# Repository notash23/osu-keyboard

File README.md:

# osu-keyboard

This is a keyboard with two assignable buttons. It has been built using RP2040. It also has two customizable RGB backlights.

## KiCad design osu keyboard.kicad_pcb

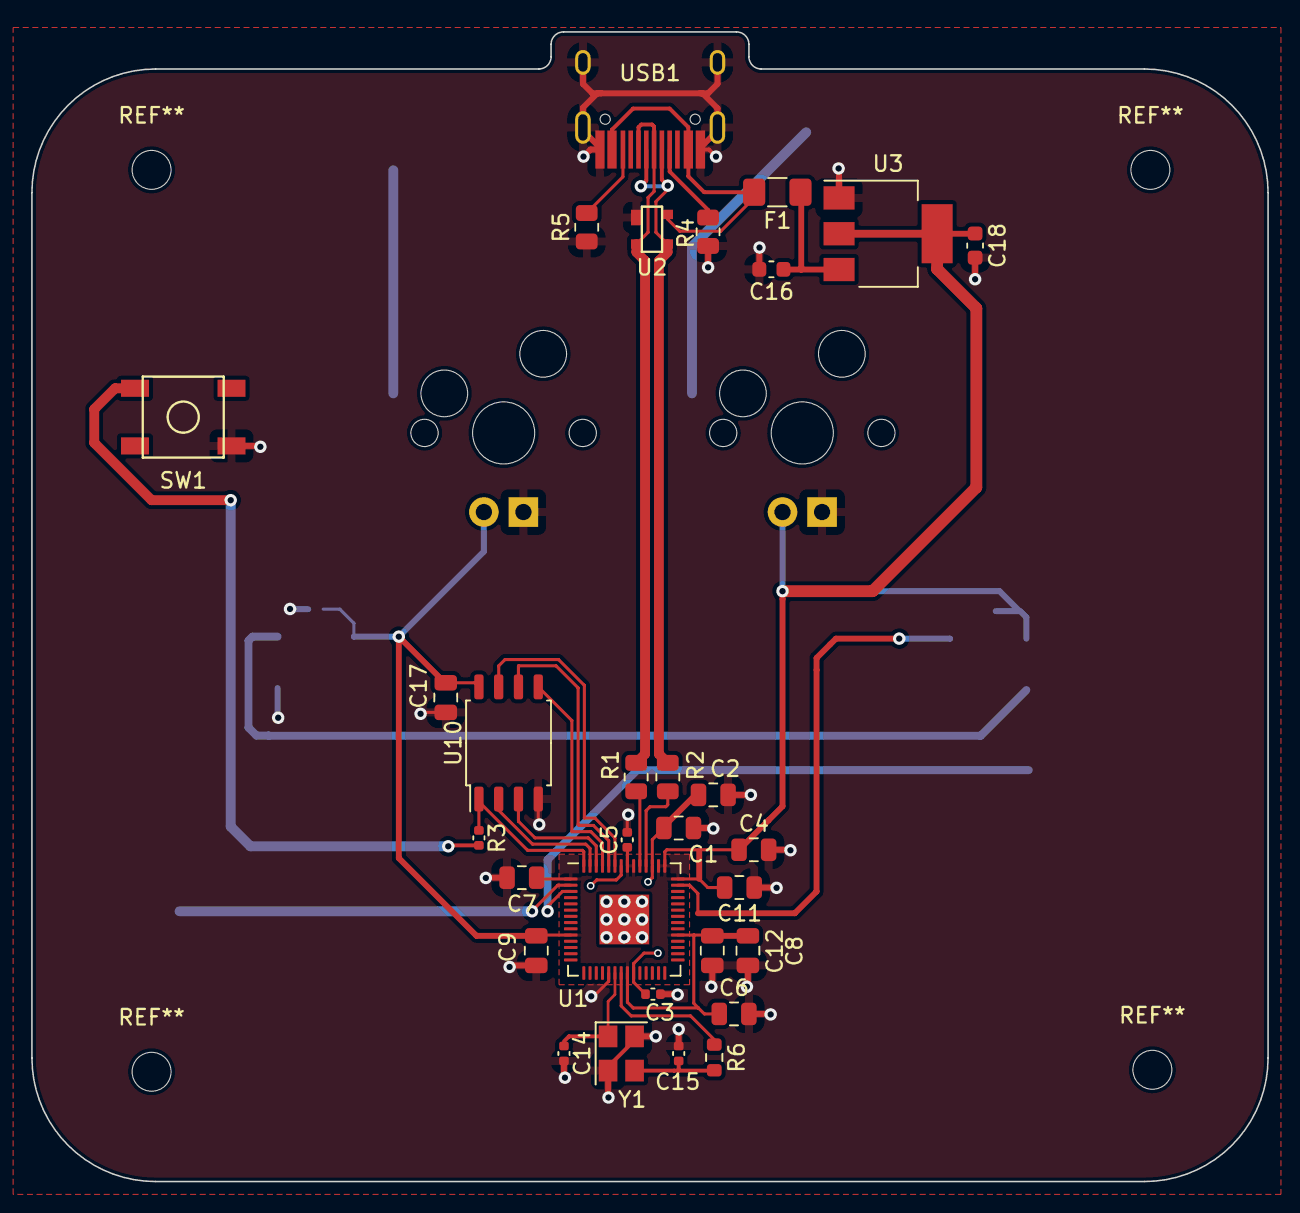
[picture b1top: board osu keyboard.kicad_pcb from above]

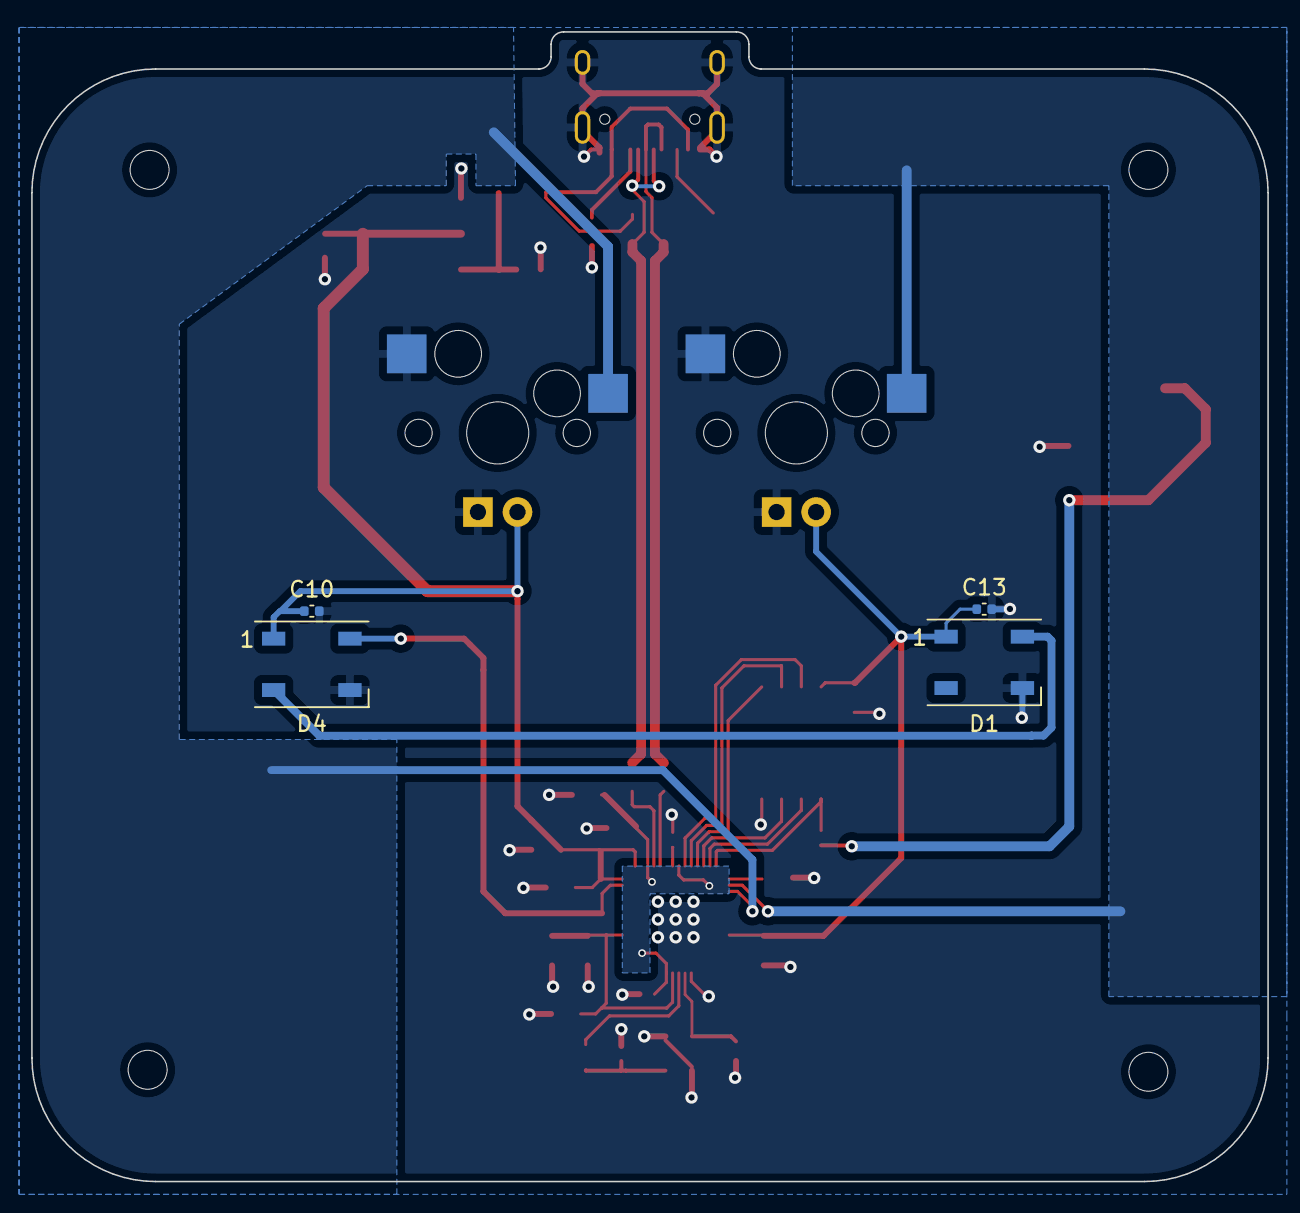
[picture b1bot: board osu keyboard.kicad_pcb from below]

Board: 2 copper layers, 79.4 x 73.8 mm, 36 parts (4 on the bottom side), 25 nets.

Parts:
C1, C2, C4, C6, C7, C8, C9, C11, C12, C17: 100nF; C_0805_2012Metric
C3, C5: 1uF; C_0402_1005Metric
C10, C13: 100nF; C_0402_1005Metric
C14, C15: 14pF; C_0402_1005Metric
C16, C18: 22uF; C_0603_1608Metric
D1, D4: WS2812B; LED_WS2812B_PLCC4_5.0x5.0mm_P3.2mm
F1: Polyfuse_Small; Fuse_1206_3216Metric_Pad1.42x1.75mm_HandSolder
MX0, MX1: MX-LED; MXOnly-1U-Hotswap-LED
R1, R2: 27; R_0805_2012Metric
R3: 1k; C_0402_1005Metric
R4, R5: 5.1k; R_0805_2012Metric
R6: 1k; R_0603_1608Metric
SW1: SW_Push; SKQG-1155865
U1: RP2040; QFN-56-1EP_7x7mm_P0.4mm_EP3.2x3.2mm
U2: PRTR5V0U2X; SOT143B
U3: AMS1117-3.3; SOT-223-3_TabPin2
U10: W25Q128JVS; SOIC-8_5.23x5.23mm_P1.27mm
USB1: HRO-TYPE-C-31-M-12; HRO-TYPE-C-31-M-12-HandSoldering
Y1: 12MHz; Crystal_SMD_3225-4Pin_3.2x2.5mm

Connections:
+1V1: C1.1, C2.1, C3.1, U1.23 (DVDD), U1.45 (VREG_VOUT), U1.50 (DVDD)
+3V3: C4.1, C5.1, C6.1, C7.1, C8.1, C9.1, C10.2, C11.1, C12.1, C13.2, C17.1, C18.1, D1.1 (VDD), D4.1 (VDD), MX0.3 (LED), MX1.3 (LED), U1.1 (IOVDD), U1.10 (IOVDD), U1.22 (IOVDD), U1.33 (IOVDD), U1.42 (IOVDD), U1.43 (ADC_AVDD), U1.44 (VREG_IN), U1.48 (USB_VDD), U1.49 (IOVDD), U3.2 (VO), U10.8 (VCC)
/COL0: MX0.1 (COL), U1.2 (GPIO0)
/COL1: MX1.1 (COL), U1.3 (GPIO1)
/D+: R1.1, U2.2 (IO1), USB1.6 (DP1), USB1.8 (DP2)
/D-: R2.1, U2.3 (IO2), USB1.5 (DN2), USB1.7 (DN1)
/QSPI_SCLK: U1.52 (QSPI_SCLK), U10.6 (CLK)
/QSPI_SD0: U1.53 (QSPI_SD0), U10.5 (DI(IO0))
/QSPI_SD1: U1.55 (QSPI_SD1), U10.2 (DO(IO1))
/QSPI_SD2: U1.54 (QSPI_SD2), U10.3 (IO2)
/QSPI_SD3: U1.51 (QSPI_SD3), U10.7 (IO3)
/QSPI_SS: R3.1, U1.56 (QSPI_SS), U10.1 (~CS)
/REG: C16.1, F1.1, U3.3 (VI)
/UNDERGLOWLED: D4.4 (DIN), U1.41 (GPIO29_ADC3)
/XIN: C14.1, U1.20 (XIN), Y1.1
/XOUT: R6.1, U1.21 (XOUT)
GND: C1.2, C2.2, C3.2, C4.2, C5.2, C6.2, C7.2, C8.2, C9.2, C10.1, C11.2, C12.2, C13.1, C14.2, C15.2, C16.2, C17.2, C18.2, D1.3 (VSS), D4.3 (VSS), MX0.2 (ROW), MX0.4 (LEDGND), MX1.2 (ROW), MX1.4 (LEDGND), R4.1, R5.1, SW1.1, U1.19 (TESTEN), U1.57 (GND), U2.1 (GND), U3.1 (GND), U10.4 (GND), USB1.1 (GND), USB1.12 (GND), USB1.13 (SHIELD), Y1.2, Y1.4
unnamed: C15.1, R6.2, Y1.3
unnamed: D1.4 (DIN), D4.2 (DOUT)
unnamed: R1.2, U1.47 (USB_DP)
unnamed: R2.2, U1.46 (USB_DM)
unnamed: R3.2, SW1.2
unnamed: R4.2, USB1.4 (CC1)
unnamed: R5.2, USB1.10 (CC2)
VCC: F1.2, U2.4 (VCC), USB1.2 (VBUS), USB1.11 (VBUS)

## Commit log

2022-11-05 added submodules
2022-11-05 added schematics and footlibs
2022-11-05 Added Type-C
2022-11-06 Schematics
2022-11-06 pcb setup arranged
2022-11-07 added pcb
2022-11-13 using rp2040
